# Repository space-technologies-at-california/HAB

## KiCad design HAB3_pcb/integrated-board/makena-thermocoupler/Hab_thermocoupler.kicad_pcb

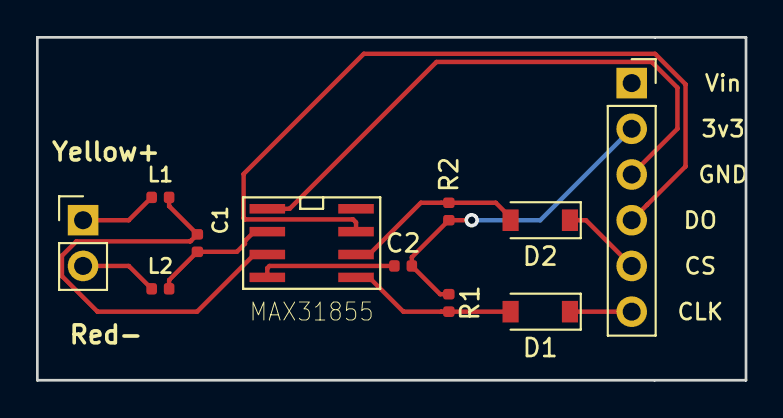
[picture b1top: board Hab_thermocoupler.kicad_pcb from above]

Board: 4 copper layers, 39.4 x 19.0 mm, 11 parts (0 on the bottom side), 12 nets.

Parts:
C1: .01 uF; C_0402_1005Metric
C2: 0.1 uF; C_0402_1005Metric
D1, D2: 1N4148; D_SOD-123
J1: Conn_01x02_Male; PinHeader_1x02_P2.54mm_Vertical
J2: Conn_01x06_Female; PinSocket_1x06_P2.54mm_Vertical
L1, L2: Ferrite_Bead; L_0402_1005Metric
R1, R2: 10k; R_0402_1005Metric
U1: MAX31855; SO-8

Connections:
GND: J2.3, U1.1
unnamed: C1.1, L1.1, U1.3
unnamed: C1.2, L2.1, U1.2
unnamed: C2.1, U1.4
unnamed: C2.2, J2.2, R1.1, R2.2
unnamed: D1.1, J2.6
unnamed: D1.2, R1.2, U1.5
unnamed: D2.1, J2.5
unnamed: D2.2, R2.1, U1.6
unnamed: J1.1, L1.2
unnamed: J1.2, L2.2
unnamed: J2.4, U1.7

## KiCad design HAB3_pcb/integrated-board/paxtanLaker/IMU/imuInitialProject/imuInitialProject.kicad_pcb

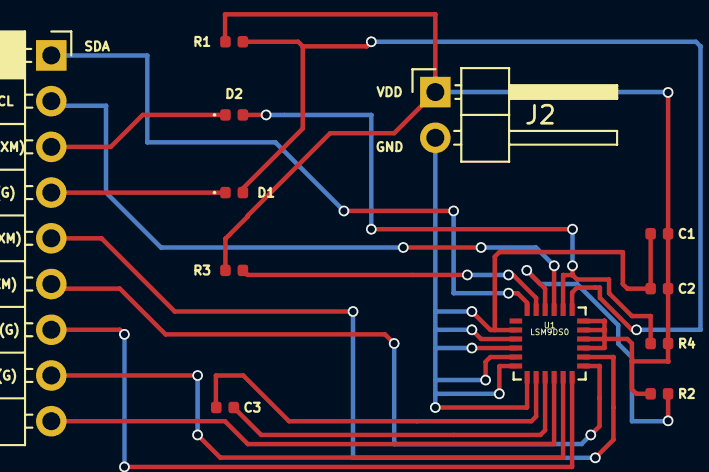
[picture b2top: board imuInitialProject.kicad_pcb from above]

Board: 4 copper layers, 12 parts (0 on the bottom side), 17 nets.

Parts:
C1: 100nF; C_0402_1005Metric
C2: 10uF; C_0402_1005Metric
C3: 0.22uF; C_0402_1005Metric
D1, D2: D_Small; D_0402_1005Metric
J1: Conn_01x09_Female; PinSocket_1x09_P2.54mm_Horizontal
J2: Conn_01x02_Female; PinHeader_1x02_P2.54mm_Horizontal
R1, R2, R3, R4: 10k; R_0402_1005Metric
U1: LSM9DS0; LGA-24LSM

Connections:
unnamed: C1.1, C2.1, J2.2, U1.2, U1.3, U1.4, U1.5, U1.6, U1.7
unnamed: C1.2, C2.2, J2.1, R1.1, R2.1, R3.1, R4.2, U1.15, U1.16, U1.17, U1.18
unnamed: C3.1, U1.8
unnamed: C3.2, U1.9
unnamed: D1.1, J1.4
unnamed: D1.2, R1.2, U1.19
unnamed: D2.1, J1.3
unnamed: D2.2, R4.1, U1.20
unnamed: J1.1, U1.24
unnamed: J1.2, U1.21
unnamed: J1.5, U1.14
unnamed: J1.6, U1.13
unnamed: J1.7, U1.12
unnamed: J1.8, U1.11
unnamed: J1.9, U1.10
unnamed: R2.2, U1.22
unnamed: R3.2, U1.23

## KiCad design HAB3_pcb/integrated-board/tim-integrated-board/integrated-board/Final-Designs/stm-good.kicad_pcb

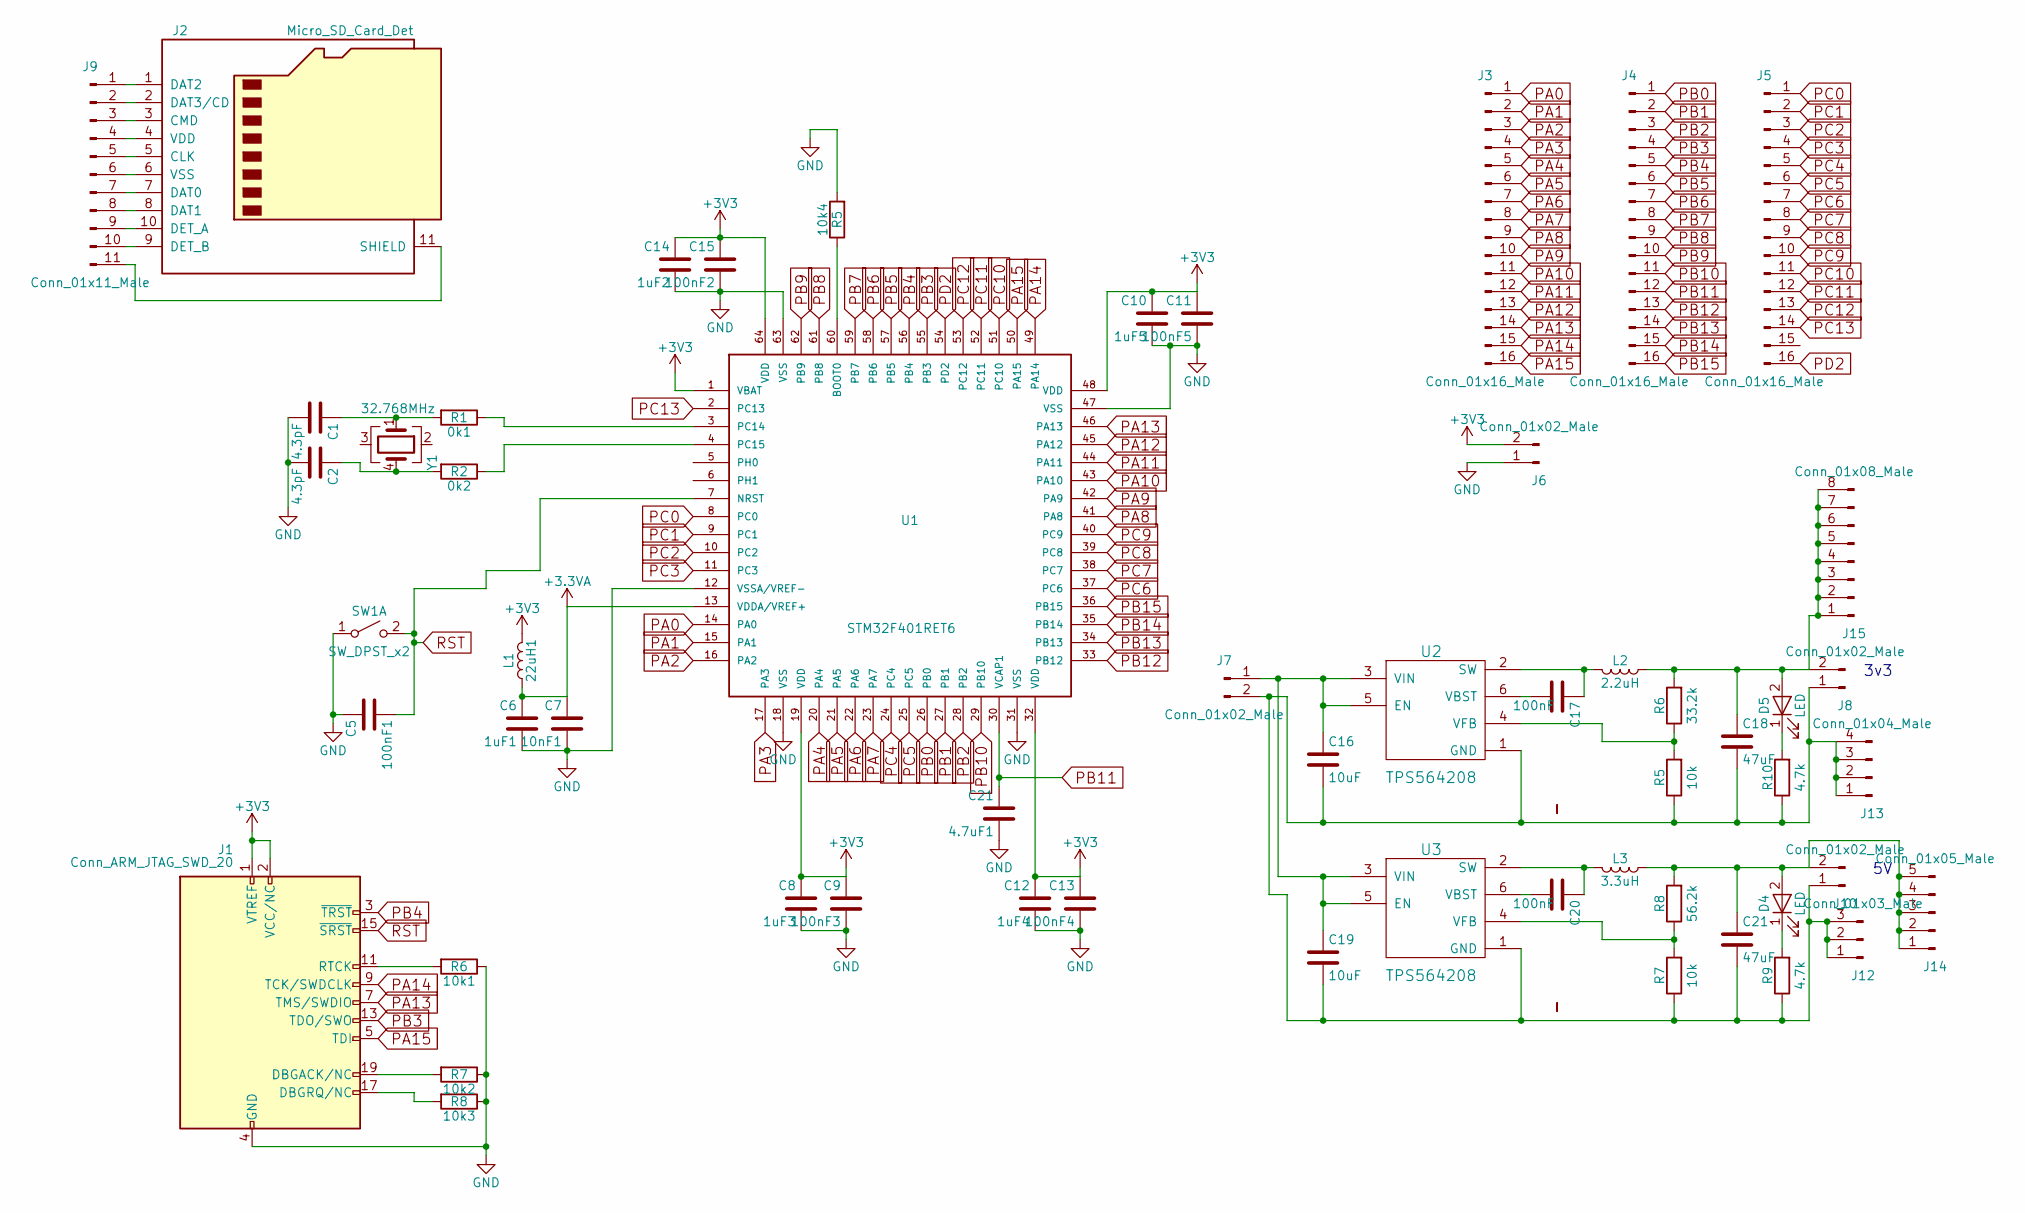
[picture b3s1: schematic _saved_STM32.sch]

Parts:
0k1: R1; R_0603_HandSoldering
0k2: R2; R_0603_HandSoldering
1uF1: C6; C_0603_HandSoldering
1uF2: C14; C_0603_HandSoldering
1uF3: C8; C_0603_HandSoldering
1uF4: C12; C_0603_HandSoldering
1uF5: C10; C_0603_HandSoldering
4.7uF1: C21; C_0603_HandSoldering
10k1: R6; R_0603_HandSoldering
10k2: R7; R_0603_HandSoldering
10k3: R8; R_0603_HandSoldering
10k4: R5; R_0603_HandSoldering
10nF1: C7; C_0603_HandSoldering
22uH1: L1; L_0603_HandSoldering
100nF1: C5; C_0603_HandSoldering
100nF2: C15; C_0603_HandSoldering
100nF3: C9; C_0603_HandSoldering
100nF4: C13; C_0603_HandSoldering
100nF5: C11; C_0603_HandSoldering
C1, C2: 4.3pF; C_0603_HandSoldering
C16, C19: 10uF; C_0603_HandSoldering
C17, C20: 100nF; C_0603_HandSoldering
C18, C21: 47uF; C_0603_HandSoldering
D4, D5: LED; LED_0603_HandSoldering
J1: Conn_ARM_JTAG_SWD_20; Pin_Header_Straight_2x10_Pitch2.54mm
J2: Micro_SD_Card_Det; Hirose_DM3BT-DSF-PEJS
J3, J4, J5: Conn_01x16_Male; Pin_Header_Straight_1x16_Pitch2.54mm
J6, J7, J8, J10: Conn_01x02_Male; Pin_Header_Straight_1x02_Pitch2.54mm
J9: Conn_01x11_Male; Pin_Header_Straight_1x11_Pitch2.54mm
J12: Conn_01x03_Male; Pin_Header_Straight_1x03_Pitch2.54mm
J13: Conn_01x04_Male; Pin_Header_Straight_1x04_Pitch2.54mm
J14: Conn_01x05_Male; Pin_Header_Straight_1x05_Pitch2.54mm
J15: Conn_01x08_Male; Pin_Header_Straight_1x08_Pitch2.54mm
L2: 2.2uH; INDC7070X450
L3: 3.3uH; INDC7070X450
R5, R7: 10k; R_0603_HandSoldering
R6: 33.2k; R_0603_HandSoldering
R8: 56.2k; R_0603_HandSoldering
R9, R10: 4.7k; R_0603_HandSoldering
SW1: SW_DPST_x2; SW_SPST_B3U-1000P
U1: STM32F401RET6; QFP50P1200X1200X160-64N
U2, U3: TPS564208
Y1: 32.768MHz; Crystal_SMD_0603-4pin_6.0x3.5mm_HandSoldering

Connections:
+3.3VA: 1uF1.2, 10nF1.2, 22uH1.1, U1.13 (VDDA/VREF+)
+3V3: 1uF2.2, 1uF3.2, 1uF4.2, 1uF5.2, 22uH1.2, 100nF2.2, 100nF3.2, 100nF4.2, 100nF5.2, J1.1 (VTREF), J1.2 (VCC/NC), J6.2, U1.1 (VBAT), U1.19 (VDD), U1.32 (VDD), U1.48 (VDD), U1.64 (VDD)
GND: 1uF1.1, 1uF2.1, 1uF3.1, 1uF4.1, 1uF5.1, 4.7uF1.1, 10k1.1, 10k2.1, 10k3.1, 10k4.2, 10nF1.1, 100nF1.2, 100nF2.1, 100nF3.1, 100nF4.1, 100nF5.1, C1.2, C2.2, J1.4 (GND), J1.6 (GND), J1.8 (GND), J1.10 (GND), J1.12 (GND), J1.14 (GND), J1.16 (GND), J1.18 (GND), J1.20 (GND), J6.1, SW1.1 (A), U1.12 (VSSA/VREF-), U1.18 (VSS), U1.31 (VSS), U1.47 (VSS), U1.63 (VSS)
unnamed: 0k1.1, U1.3 (PC14)
unnamed: 0k1.2, C1.1, Y1.1
unnamed: 0k2.1, U1.4 (PC15)
unnamed: 0k2.2, C2.1, Y1.4
unnamed: 10k1.2, J1.11 (RTCK)
unnamed: 10k2.2, J1.19 (DBGACK/NC)
unnamed: 10k3.2, J1.17 (DBGRQ/NC)
unnamed: 10k4.1, U1.60 (BOOT0)
unnamed: C16.1, C19.1, J7.1, U2.3 (VIN), U2.5 (EN), U3.3 (VIN), U3.5 (EN)
unnamed: C16.2, C18.2, C19.2, C21.2, J7.2, J8.1, J10.1, J12.1, J12.2, J12.3, J13.1, J13.2, J13.3, J13.4, R5.1, R7.1, R9.1, R10.1, U2.1 (GND), U3.1 (GND)
unnamed: C17.1, L2.2, U2.2 (SW)
unnamed: C17.2, U2.6 (VBST)
unnamed 15: C18.1, D5.2 (A), J8.2, J15.1, J15.2, J15.3, J15.4, J15.5, J15.6, J15.7, J15.8, L2.1, R6.2; also elsewhere on the board
unnamed: C20.1, L3.2, U3.2 (SW)
unnamed: C20.2, U3.6 (VBST)
unnamed: C21.1, D4.2 (A), J10.2, J14.1, J14.2, J14.3, J14.4, J14.5, L3.1, R8.2
unnamed: D4.1 (K), R9.2
unnamed: D5.1 (K), R10.2
unnamed: J2.1 (DAT2), J9.1
unnamed: J2.2 (DAT3/CD), J9.2
unnamed: J2.3 (CMD), J9.3
unnamed: J2.4 (VDD), J9.4
unnamed: J2.5 (CLK), J9.5
unnamed: J2.6 (VSS), J9.6
unnamed: J2.7 (DAT0), J9.7
unnamed: J2.8 (DAT1), J9.8
unnamed: J2.9 (DET_B), J9.10
unnamed: J2.10 (DET_A), J9.9
unnamed: J2.11 (SHIELD), J9.11
unnamed: R5.2, R6.1, U2.4 (VFB)
unnamed: R7.2, R8.1, U3.4 (VFB)
PA0: J3.1, U1.14 (PA0)
PA1: J3.2, U1.15 (PA1)
PA2: J3.3, U1.16 (PA2)
PA3: J3.4, U1.17 (PA3)
PA4: J3.5, U1.20 (PA4)
PA5: J3.6, U1.21 (PA5)
PA6: J3.7, U1.22 (PA6)
PA7: J3.8, U1.23 (PA7)
PA8: J3.9, U1.41 (PA8)
PA9: J3.10, U1.42 (PA9)
PA10: J3.11, U1.43 (PA10)
PA11: J3.12, U1.44 (PA11)
PA12: J3.13, U1.45 (PA12)
PA13: J1.7 (TMS/SWDIO), J3.14, U1.46 (PA13)
PA14: J1.9 (TCK/SWDCLK), J3.15, U1.49 (PA14)
PA15: J1.5 (TDI), J3.16, U1.50 (PA15)
PB0: J4.1, U1.26 (PB0)
PB1: J4.2, U1.27 (PB1)
PB2: J4.3, U1.28 (PB2)
PB3: J1.13 (TDO/SWO), J4.4, U1.55 (PB3)
PB4: J1.3 (~TRST~), J4.5, U1.56 (PB4)
PB5: J4.6, U1.57 (PB5)
PB6: J4.7, U1.58 (PB6)
PB7: J4.8, U1.59 (PB7)
PB8: J4.9, U1.61 (PB8)
PB9: J4.10, U1.62 (PB9)
PB10: J4.11, U1.29 (PB10)
PB11: 4.7uF1.2, J4.12, U1.30 (VCAP1)
PB12: J4.13, U1.33 (PB12)
PB13: J4.14, U1.34 (PB13)
PB14: J4.15, U1.35 (PB14)
PB15: J4.16, U1.36 (PB15)
PC0: J5.1, U1.8 (PC0)
PC1: J5.2, U1.9 (PC1)
PC2: J5.3, U1.10 (PC2)
PC3: J5.4, U1.11 (PC3)
PC4: J5.5, U1.24 (PC4)
PC5: J5.6, U1.25 (PC5)
PC6: J5.7, U1.37 (PC6)
PC7: J5.8, U1.38 (PC7)
PC8: J5.9, U1.39 (PC8)
PC9: J5.10, U1.40 (PC9)
PC10: J5.11, U1.51 (PC10)
PC11: J5.12, U1.52 (PC11)
PC12: J5.13, U1.53 (PC12)
PC13: J5.14, U1.2 (PC13)
PD2: J5.16, U1.54 (PD2)
RST: 100nF1.1, J1.15 (~SRST~), SW1.2 (B), U1.7 (NRST)

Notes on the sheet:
3v3

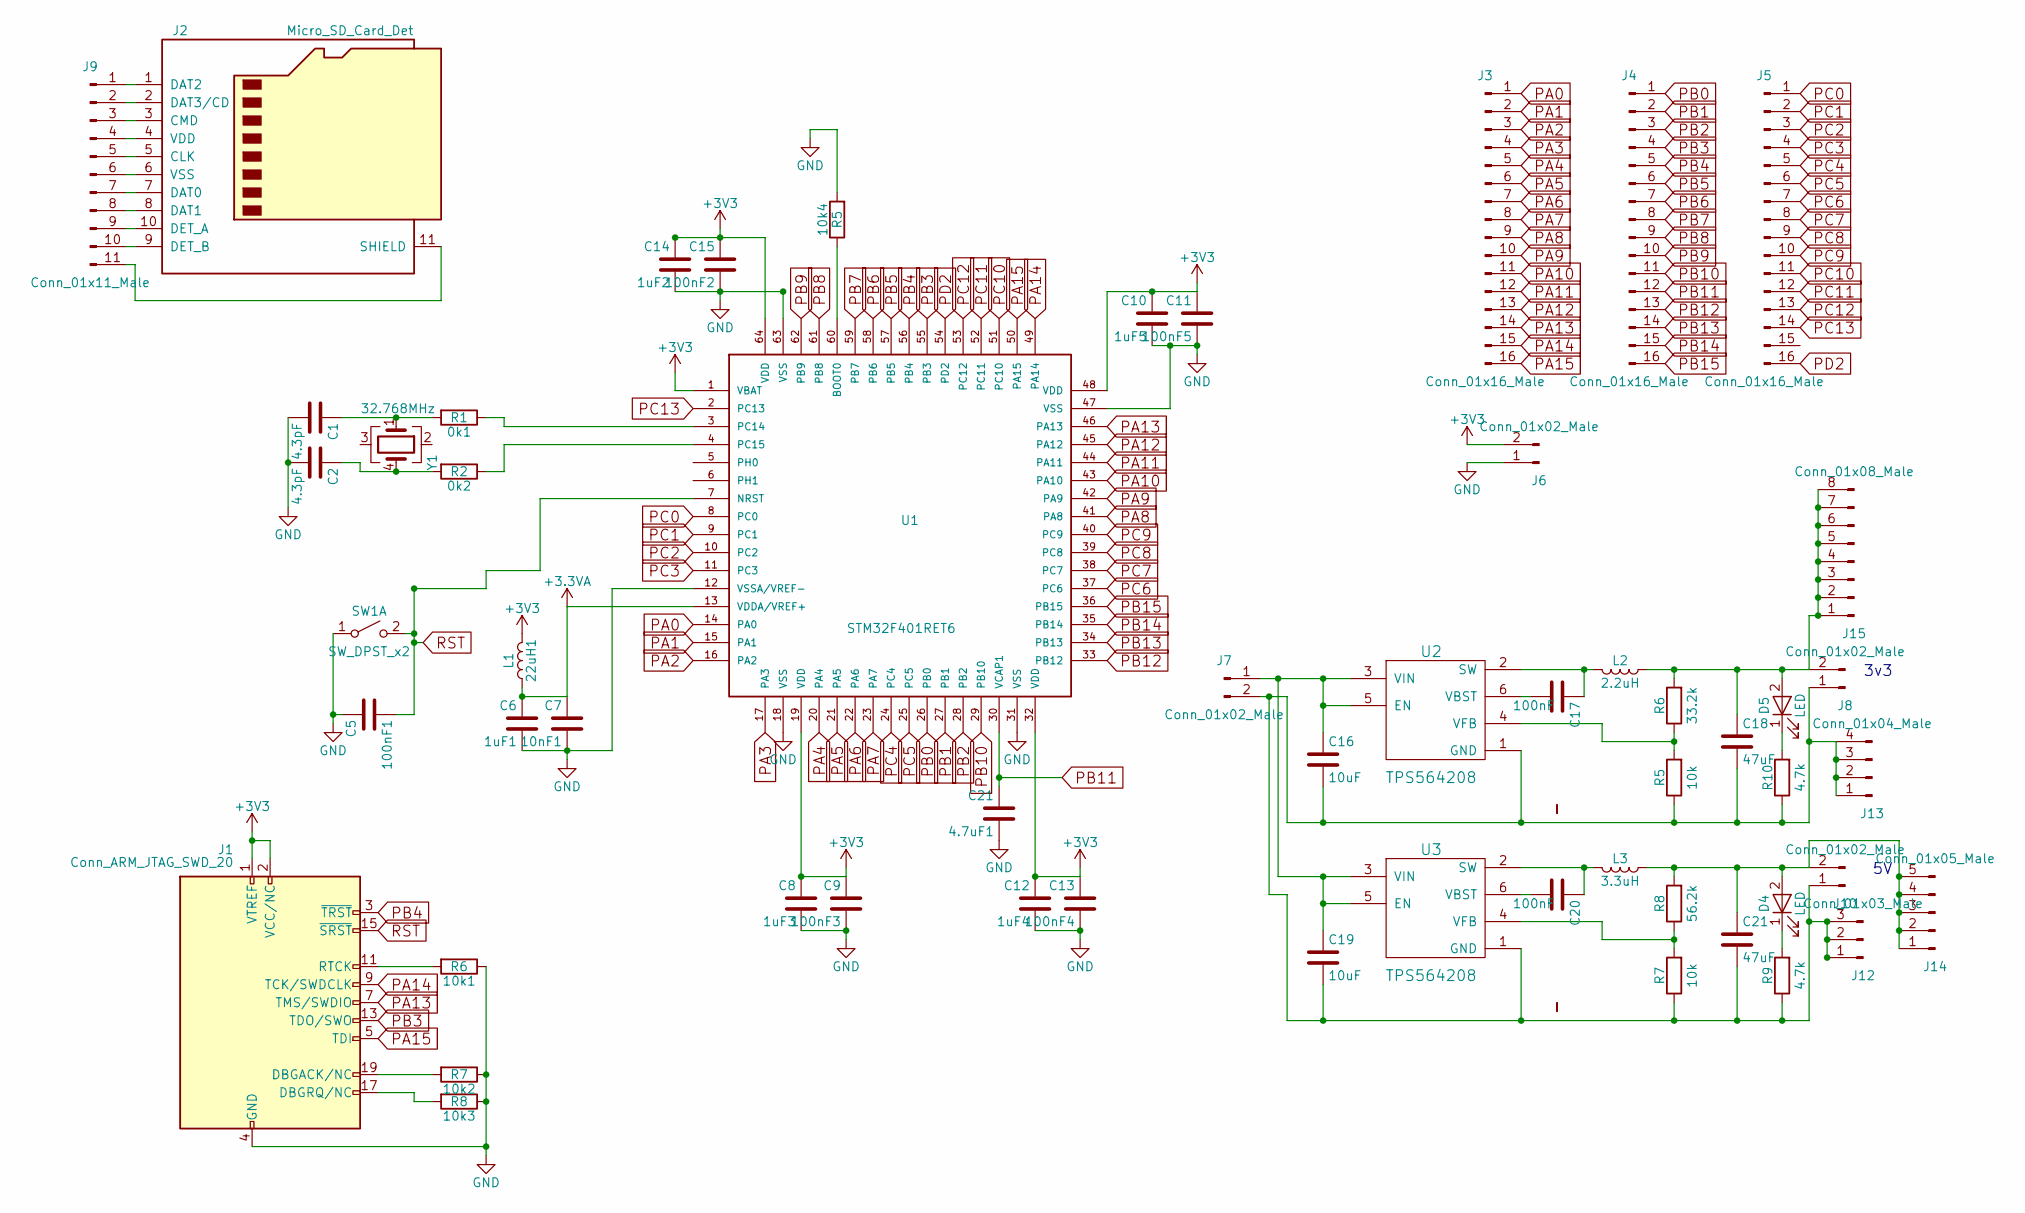
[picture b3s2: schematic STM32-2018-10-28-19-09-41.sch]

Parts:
0k1: R1; R_0603_HandSoldering
0k2: R2; R_0603_HandSoldering
1uF1: C6; C_0603_HandSoldering
1uF2: C14; C_0603_HandSoldering
1uF3: C8; C_0603_HandSoldering
1uF4: C12; C_0603_HandSoldering
1uF5: C10; C_0603_HandSoldering
4.7uF1: C21; C_0603_HandSoldering
10k1: R6; R_0603_HandSoldering
10k2: R7; R_0603_HandSoldering
10k3: R8; R_0603_HandSoldering
10k4: R5; R_0603_HandSoldering
10nF1: C7; C_0603_HandSoldering
22uH1: L1; L_0603_HandSoldering
100nF1: C5; C_0603_HandSoldering
100nF2: C15; C_0603_HandSoldering
100nF3: C9; C_0603_HandSoldering
100nF4: C13; C_0603_HandSoldering
100nF5: C11; C_0603_HandSoldering
C1, C2: 4.3pF; C_0603_HandSoldering
C16, C19: 10uF; C_0603_HandSoldering
C17, C20: 100nF; C_0603_HandSoldering
C18, C21: 47uF; C_0603_HandSoldering
D4, D5: LED; LED_0603_HandSoldering
J1: Conn_ARM_JTAG_SWD_20; Pin_Header_Straight_2x10_Pitch2.54mm
J2: Micro_SD_Card_Det; Hirose_DM3BT-DSF-PEJS
J3, J4, J5: Conn_01x16_Male; Pin_Header_Straight_1x16_Pitch2.54mm
J6, J7, J8, J10: Conn_01x02_Male; Pin_Header_Straight_1x02_Pitch2.54mm
J9: Conn_01x11_Male; Pin_Header_Straight_1x11_Pitch2.54mm
J12: Conn_01x03_Male; Pin_Header_Straight_1x03_Pitch2.54mm
J13: Conn_01x04_Male; Pin_Header_Straight_1x04_Pitch2.54mm
J14: Conn_01x05_Male; Pin_Header_Straight_1x05_Pitch2.54mm
J15: Conn_01x08_Male; Pin_Header_Straight_1x08_Pitch2.54mm
L2: 2.2uH; INDC7070X450
L3: 3.3uH; INDC7070X450
R5, R7: 10k; R_0603_HandSoldering
R6: 33.2k; R_0603_HandSoldering
R8: 56.2k; R_0603_HandSoldering
R9, R10: 4.7k; R_0603_HandSoldering
SW1: SW_DPST_x2; SW_SPST_B3U-1000P
U1: STM32F401RET6; QFP50P1200X1200X160-64N
U2, U3: TPS564208
Y1: 32.768MHz; Crystal_SMD_0603-4pin_6.0x3.5mm_HandSoldering

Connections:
+3.3VA: 1uF1.2, 10nF1.2, 22uH1.1, U1.13 (VDDA/VREF+)
+3V3: 1uF2.2, 1uF3.2, 1uF4.2, 1uF5.2, 22uH1.2, 100nF2.2, 100nF3.2, 100nF4.2, 100nF5.2, J1.1 (VTREF), J1.2 (VCC/NC), J6.2, U1.1 (VBAT), U1.19 (VDD), U1.32 (VDD), U1.48 (VDD), U1.64 (VDD)
GND: 1uF1.1, 1uF2.1, 1uF3.1, 1uF4.1, 1uF5.1, 4.7uF1.1, 10k1.1, 10k2.1, 10k3.1, 10k4.2, 10nF1.1, 100nF1.2, 100nF2.1, 100nF3.1, 100nF4.1, 100nF5.1, C1.2, C2.2, J1.4 (GND), J1.6 (GND), J1.8 (GND), J1.10 (GND), J1.12 (GND), J1.14 (GND), J1.16 (GND), J1.18 (GND), J1.20 (GND), J6.1, SW1.1 (A), U1.12 (VSSA/VREF-), U1.18 (VSS), U1.31 (VSS), U1.47 (VSS), U1.63 (VSS)
unnamed: 0k1.1, U1.3 (PC14)
unnamed: 0k1.2, C1.1, Y1.1
unnamed: 0k2.1, U1.4 (PC15)
unnamed: 0k2.2, C2.1, Y1.4
unnamed: 10k1.2, J1.11 (RTCK)
unnamed: 10k2.2, J1.19 (DBGACK/NC)
unnamed: 10k3.2, J1.17 (DBGRQ/NC)
unnamed: 10k4.1, U1.60 (BOOT0)
unnamed: C16.1, C19.1, J7.1, U2.3 (VIN), U2.5 (EN), U3.3 (VIN), U3.5 (EN)
unnamed: C16.2, C18.2, C19.2, C21.2, J7.2, J8.1, J10.1, J12.1, J12.2, J12.3, J13.1, J13.2, J13.3, J13.4, R5.1, R7.1, R9.1, R10.1, U2.1 (GND), U3.1 (GND)
unnamed: C17.1, L2.2, U2.2 (SW)
unnamed: C17.2, U2.6 (VBST)
unnamed 15: C18.1, D5.2 (A), J8.2, J15.1, J15.2, J15.3, J15.4, J15.5, J15.6, J15.7, J15.8, L2.1, R6.2; also elsewhere on the board
unnamed: C20.1, L3.2, U3.2 (SW)
unnamed: C20.2, U3.6 (VBST)
unnamed: C21.1, D4.2 (A), J10.2, J14.1, J14.2, J14.3, J14.4, J14.5, L3.1, R8.2
unnamed: D4.1 (K), R9.2
unnamed: D5.1 (K), R10.2
unnamed: J2.1 (DAT2), J9.1
unnamed: J2.2 (DAT3/CD), J9.2
unnamed: J2.3 (CMD), J9.3
unnamed: J2.4 (VDD), J9.4
unnamed: J2.5 (CLK), J9.5
unnamed: J2.6 (VSS), J9.6
unnamed: J2.7 (DAT0), J9.7
unnamed: J2.8 (DAT1), J9.8
unnamed: J2.9 (DET_B), J9.10
unnamed: J2.10 (DET_A), J9.9
unnamed: J2.11 (SHIELD), J9.11
unnamed: R5.2, R6.1, U2.4 (VFB)
unnamed: R7.2, R8.1, U3.4 (VFB)
PA0: J3.1, U1.14 (PA0)
PA1: J3.2, U1.15 (PA1)
PA2: J3.3, U1.16 (PA2)
PA3: J3.4, U1.17 (PA3)
PA4: J3.5, U1.20 (PA4)
PA5: J3.6, U1.21 (PA5)
PA6: J3.7, U1.22 (PA6)
PA7: J3.8, U1.23 (PA7)
PA8: J3.9, U1.41 (PA8)
PA9: J3.10, U1.42 (PA9)
PA10: J3.11, U1.43 (PA10)
PA11: J3.12, U1.44 (PA11)
PA12: J3.13, U1.45 (PA12)
PA13: J1.7 (TMS/SWDIO), J3.14, U1.46 (PA13)
PA14: J1.9 (TCK/SWDCLK), J3.15, U1.49 (PA14)
PA15: J1.5 (TDI), J3.16, U1.50 (PA15)
PB0: J4.1, U1.26 (PB0)
PB1: J4.2, U1.27 (PB1)
PB2: J4.3, U1.28 (PB2)
PB3: J1.13 (TDO/SWO), J4.4, U1.55 (PB3)
PB4: J1.3 (~TRST~), J4.5, U1.56 (PB4)
PB5: J4.6, U1.57 (PB5)
PB6: J4.7, U1.58 (PB6)
PB7: J4.8, U1.59 (PB7)
PB8: J4.9, U1.61 (PB8)
PB9: J4.10, U1.62 (PB9)
PB10: J4.11, U1.29 (PB10)
PB11: 4.7uF1.2, J4.12, U1.30 (VCAP1)
PB12: J4.13, U1.33 (PB12)
PB13: J4.14, U1.34 (PB13)
PB14: J4.15, U1.35 (PB14)
PB15: J4.16, U1.36 (PB15)
PC0: J5.1, U1.8 (PC0)
PC1: J5.2, U1.9 (PC1)
PC2: J5.3, U1.10 (PC2)
PC3: J5.4, U1.11 (PC3)
PC4: J5.5, U1.24 (PC4)
PC5: J5.6, U1.25 (PC5)
PC6: J5.7, U1.37 (PC6)
PC7: J5.8, U1.38 (PC7)
PC8: J5.9, U1.39 (PC8)
PC9: J5.10, U1.40 (PC9)
PC10: J5.11, U1.51 (PC10)
PC11: J5.12, U1.52 (PC11)
PC12: J5.13, U1.53 (PC12)
PC13: J5.14, U1.2 (PC13)
PD2: J5.16, U1.54 (PD2)
RST: 100nF1.1, J1.15 (~SRST~), SW1.2 (B), U1.7 (NRST)

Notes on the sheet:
3v3

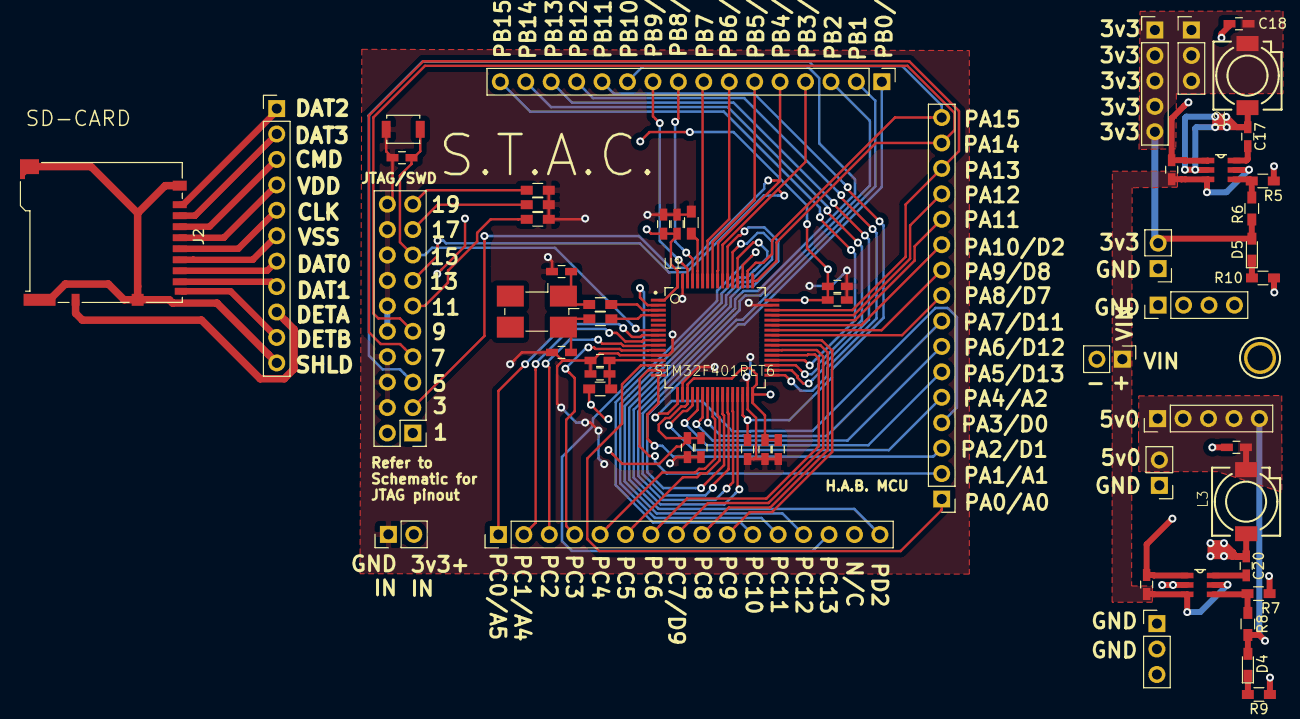
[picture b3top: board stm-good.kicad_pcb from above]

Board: 2 copper layers, 58 parts (0 on the bottom side), 82 nets.

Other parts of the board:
J20: Conn_01x03_Male; Pin_Header_Straight_1x03_Pitch2.54mm
J21: Conn_01x05_Male; Pin_Header_Straight_1x05_Pitch2.54mm
U$8: MOUNTINGHOLE2.5; MOUNTINGHOLE_2.5_PLATED

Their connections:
unnamed 15: J20.1, J20.2, J20.3, J21.1, J21.2, J21.3, J21.4, J21.5; also elsewhere on the board
